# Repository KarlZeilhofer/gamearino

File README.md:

# Gamearino

Elektronisches Spielgerät mit 
* Gameboy Tastenlayout
* OLED-Display mit 128x64 Pixel
* Controller: ESP8266EX (Modul ESP-12F)

# OLED
wurde getestet mit dem Arduino Nano mit der Adafruit-Lib. Weil wir keinen Reset-Pin haben, 
muss das Display etwas anders initialisiert werden: 
''display.begin(SSD1306_SWITCHCAPVCC, 0x3c, false);''

Die I2C-Adresse jedenfalls ist 0x3c anstatt 0x3d (Default aus Example Code). 

# Arduino IDE
* ESP8266 installieren: 
  http://arduino.esp8266.com/stable/package_esp8266com_index.json
* Adafruit SSD1306 Lib: 
  Achtung: I2C-Adresse auf 0x3c:
  #define SCREEN_ADDRESS 0x3c

  I2C-Schnittstelle auf GPIO2 und GPIO14 festlegen:
  Wire.begin(14,2); // SDA, SCL
  
# Spiele
Für diese Plattform gibt es zwei Sorten von Spielen: 
1. HTL-Spiele: Spiele von Schülern entwickelt, befindens sich in diesem Repository im Ordner "arduino": https://github.com/KarlZeilhofer/gamearino/tree/main/arduino
2. Arduboy2: Spiele von Profis programmiert. Das originale Repository wurde um die Hardwareportierung erweitert und befindet sich hier: https://github.com/KarlZeilhofer/esp8266_arduboy2

## HTL-Spiele
Für die HTL-Spiele werden folgende Bibliotheken benötigt:
* Adafruit_BusIO
* Adafruit_GFX_Library
* Adafruit_SSD1306
* ESP_EEPROM

## Arduboy Spiele
Für die Arduboy-Spiele braucht es das zweite Repository: https://github.com/KarlZeilhofer/esp8266_arduboy2 und die zugehörigen Bibliotheken, siehe README.md dort. 

# Links
* Arduino ES8266 Core Dokumentation: https://arduino-esp8266.readthedocs.io/en/latest/
* Wikipedia: https://en.wikipedia.org/wiki/ESP8266
* OLED I2C vs. SPI on Youtube: https://www.youtube.com/watch?v=Wz6Fzo3rsLM
* https://www.heise.de/ct/artikel/Arduino-IDE-installieren-und-fit-machen-fuer-ESP8266-und-ESP32-4130814.html
* http://stefanfrings.de/esp8266/
* Adafruit Graphics Library Documentation: https://learn.adafruit.com/adafruit-gfx-graphics-library/overview

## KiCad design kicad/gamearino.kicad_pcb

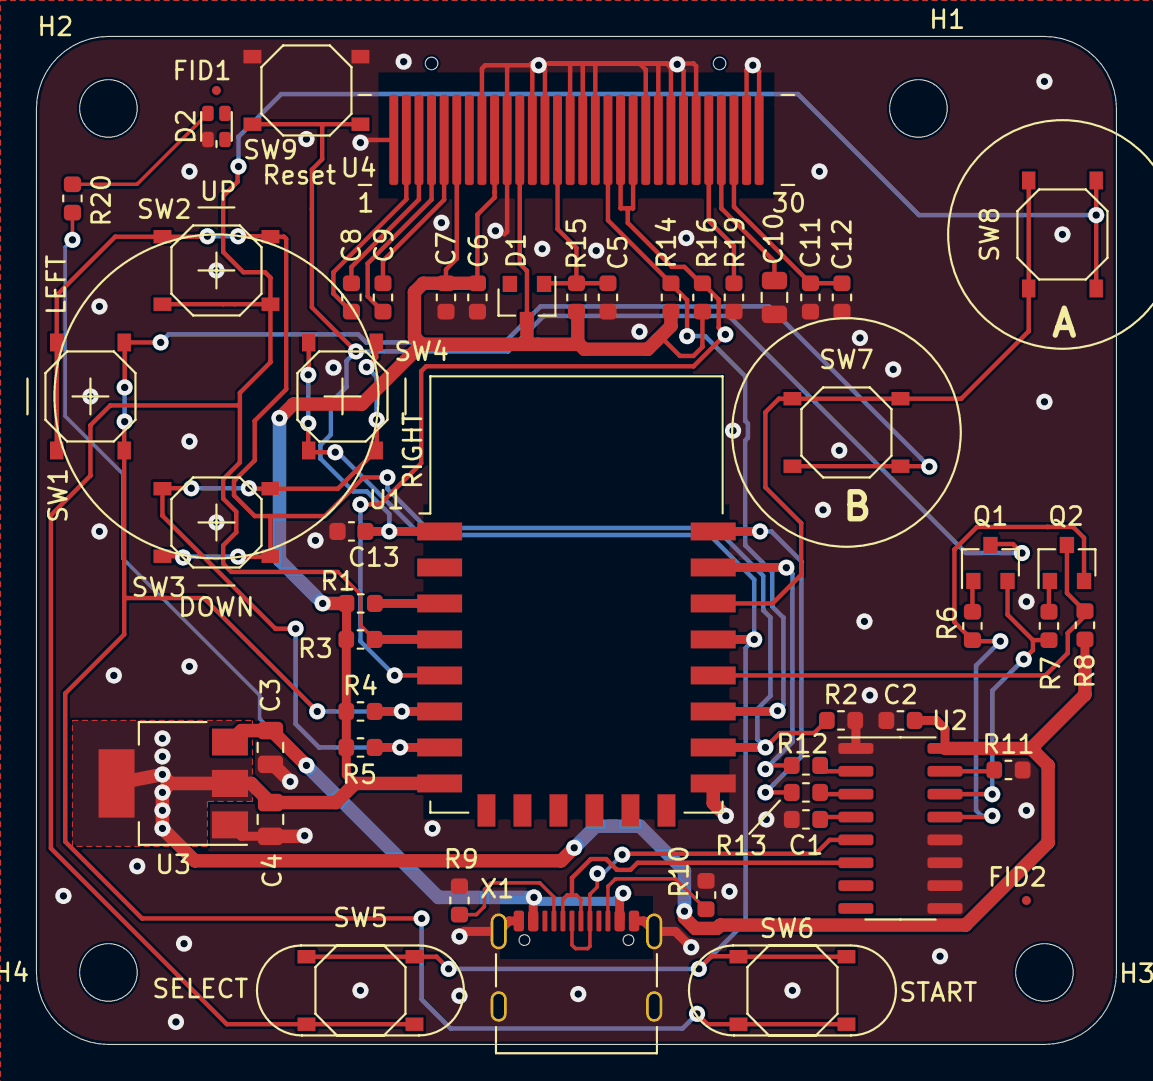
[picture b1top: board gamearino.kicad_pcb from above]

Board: 2 copper layers, 60.0 x 56.0 mm, 60 parts (0 on the bottom side), 37 nets.

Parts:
C1, C2: 100n; C_0603_1608Metric
C3, C4, C10: 10u/16V/X5R; C_0805_2012Metric
C5, C6, C7, C8, C9, C11, C12: 1u; C_0603_1608Metric
C13: DNP; C_0603_1608Metric
D1: BAV99; SOT-23
D2: LED_Dual_green-red; LED_LiteOn_LTST-C195KGJRKT
FID1, FID2: Fiducial; paste-fiducial
H1, H2, H3, H4: MountingHole; MountingHole_3.2mm_M3
Item1: 3D Druck: Knopf A; ABKnopf_v2
Item2: 3D Druck: Knopf B; ABKnopf_v2
Item3: 3D Druck: Knopf Start; StartSelect_v2
Item4: 3D Druck: Knopf Select; StartSelect_v2
Item5: 3D Druck: Steuerkreuz; Steuerkreuz_zeik_v2
Q1, Q2: PMBT3904,215; SOT-23
R1, R2, R3, R4, R5, R6, R7, R15: 10k; R_0603_1608Metric
R8, R14, R16, R20: 4k7; R_0603_1608Metric
R9, R10: 5k1; R_0603_1608Metric
R11, R12, R13: 100R; R_0603_1608Metric
R19: 910k; R_0603_1608Metric
SW1: Left; SW_Push_5.1mm_H1.5mm
SW2: Up; SW_Push_5.1mm_H1.5mm
SW3: Down; SW_Push_5.1mm_H1.5mm
SW4: Right; SW_Push_5.1mm_H1.5mm
SW5: Select; SW_Push_5.1mm_H1.5mm
SW6: Start; SW_Push_5.1mm_H1.5mm
SW7: B; SW_Push_5.1mm_H1.5mm
SW8: A; SW_Push_5.1mm_H1.5mm
SW9: Reset; SW_Push_5.1mm_H1.5mm
U1: ESP-12F
U2: CH340C; SOIC-16_3.9x9.9mm_P1.27mm
U3: AMS1117-3.3; SOT-223-3_TabPin2
U4: QG-2864KSWEG01; OLED_128x64_FlatRibbon_30
X1: USB-C/16p; USB_C_Receptacle_LCSC_C167321

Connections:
+3V3: C2.2, C4.1, C6.1, C7.1, D1.3, R1.1, R3.1, R4.1, R5.1, R8.1, R14.2, R15.1, R16.2, U1.8, U2.16, U3.2, U4.6, U4.9, U4.11
/Auto-Reset/DTR: Q2.2, R6.2, U2.13
/Auto-Reset/GPIO0: Q2.3, R8.2, U1.18
/Auto-Reset/RTS: Q1.2, R7.2, U2.14
/Buttons/C0: R2.1, SW1.1, SW2.1, SW3.1, U1.16
/Buttons/C1: SW4.1, SW5.1, SW6.1, U1.19
/Buttons/C2: SW7.1, SW8.1, U1.20
/Buttons/R0: R3.2, SW2.2, SW5.2, SW8.2, U1.4
/Buttons/R1: R4.2, SW1.2, SW6.2, SW7.2, U1.6
/Buttons/R2: R5.2, SW3.2, SW4.2, U1.7
/EN: R1.2, U1.3
/OLED 128x64/SCL: R14.1, U1.17, U4.18
/OLED 128x64/SDA: R16.1, U1.5, U4.19, U4.20
/USB/D+: U2.5, X1.A6, X1.B6
/USB/D-: U2.6, X1.A7, X1.B7
/USB/RxD: R13.1, U1.22
/USB/TxD: R12.2, U1.21
/~RESET: C13.1, Q1.3, SW9.2, U1.1
GND: C1.2, C2.1, C3.2, C4.2, C5.2, C6.2, C7.2, C10.2, C11.2, C12.2, C13.2, D2.4, R2.2, R9.1, R10.2, R11.2, R19.1, SW9.1, U1.15, U2.1, U2.9, U2.10, U2.11, U2.12, U3.1, U4.1, U4.8, U4.10, U4.12, U4.13, U4.15, U4.16, U4.17, U4.21, U4.22, U4.23, U4.24, U4.25, U4.29, U4.30, X1.A1, X1.A12, X1.B1, X1.B12, X1.S1
unnamed: C1.1, U2.4
unnamed: C3.1, R20.1, U3.3, X1.A4, X1.A9, X1.B4, X1.B9
unnamed: C5.1, D1.1, R15.2, U4.14
unnamed: C8.1, U4.2
unnamed: C8.2, U4.3
unnamed: C9.1, U4.4
unnamed: C9.2, U4.5
unnamed: C10.1, U4.27
unnamed: C11.1, C12.1, U4.28
unnamed: D2.2, R20.2
unnamed: Q1.1, R6.1
unnamed: Q2.1, R7.1
unnamed: R9.2, X1.A5
unnamed: R10.1, X1.B5
unnamed: R11.1, U2.15
unnamed: R12.1, U2.2
unnamed: R13.2, U2.3
unnamed: R19.2, U4.26

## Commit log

2020-11-09 änderungen aus werkstatt
2021-03-15 PCB-Platzierung, 3D-Knöpfe, Schaltung wird noch getestet
2021-03-15 Changelog eingeführt, GND statt GNDD
2021-03-17 usb.sch Datei war gebrochen, wurde gefixt
2021-03-17 Pinliste und kleinere Verschönerungen, Transistor-Value, ...
2021-03-17 screenshots 3D
2021-04-21 OLED funktioniert, Gehäuse vorläufig fertig
2021-04-23 Gehäuse updates, Buttons richtig zugewiesen, Tetris
2021-04-23 Snake Demo geht nun auch auf ESP
2021-04-26 v0.0.1 für CNC-Fertigung
2021-04-29 manual merge mit master
2021-04-29 Fertiges Layout v0.0.2, 3 Stk bestellt
2021-05-04 BOM fertig eingepflegt
2021-05-04 3D-Screenshot
2021-05-04 BOM für Bestellung bei LCSC nochmals korrigiert
2021-05-10 Bestellungen LCSC
2021-05-10 Button class, test buttons
2021-05-10 Soft Watchdog muss immer rückgesetzt werden
    mit delay() loop() oder millis()
2021-05-10 PCB v0.0.2 wieder hergestellt
2021-05-10 Inbetriebnahme Screenshots und Info
2021-05-10 WIP demo programme Arduino
2021-05-11 Fertige Inbetriebnahme, OLED-Beschaltung korrigiert
2021-05-11 Schaltplanänderungen für v20.0.3 eingepflegt
2021-05-11 Layoutbugfixes, v20.0.3 fertig, CAM-Daten
2021-05-11 76 Stk. bei Multi-CB bestellt
2021-05-11 Deckel und Boden optimiert, neu: Loch für Resettaster
2021-05-11 Reset-Taster gestaltet, siehe Github
    https://github.com/KarlZeilhofer/gamearino/issues/13
2021-05-13 Bisherige Funktion portiert auf Button-Klasse, Bugfix toggleText
    uint32_t für Millisekunden verwenden!
2021-05-13 Geschwindigkeitserhöhung je nach Punktestand
2021-05-14 add stateDump() for debugging
2021-05-14 Snake Bug, Issue#18 behoben
2021-05-14 Pause implementiert
2021-05-14 Highscore: EEPROM für mit der Bibliothek ESP_EEPROM
2021-05-14 Schnell Tasteneingabe verbessert
    Richtungswechsel, die momentan nicht ausgewertet werden, werden auch nicht aus den Events gelöscht, und werden im nächsten Schritt behandelt.
2021-05-14 Bugfix: manchmal gab es bisher unsichtbare Äpfel
2021-05-17 Add Graphics Documentation Link
2021-05-17 Prusa: Deckel und Boden, Produktionsstart
2021-05-31 Buttons Prusa
2021-06-07 firmware für HW-Test
2021-06-07 Buttons V3: dünner gestaltet
2021-06-07 Fullscreen Pixeltest
2021-06-09 neueste Button.cpp, verhindert kurzschlüsse von GPIOs
2021-06-09 Button Matrix Bugreport, see Github issue#20
2021-06-09 new Game: Flappy Square
2021-06-21 Prusa: steuerkreuz v2, PLA, 20er Set
2021-08-10 Update README.md, Hinweise zu Bibliotheken und Spiele
